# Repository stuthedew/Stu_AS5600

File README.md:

# Stu_AS5600
Arduino Library AS5600 12-bit Programmable Contactless Potentiometer

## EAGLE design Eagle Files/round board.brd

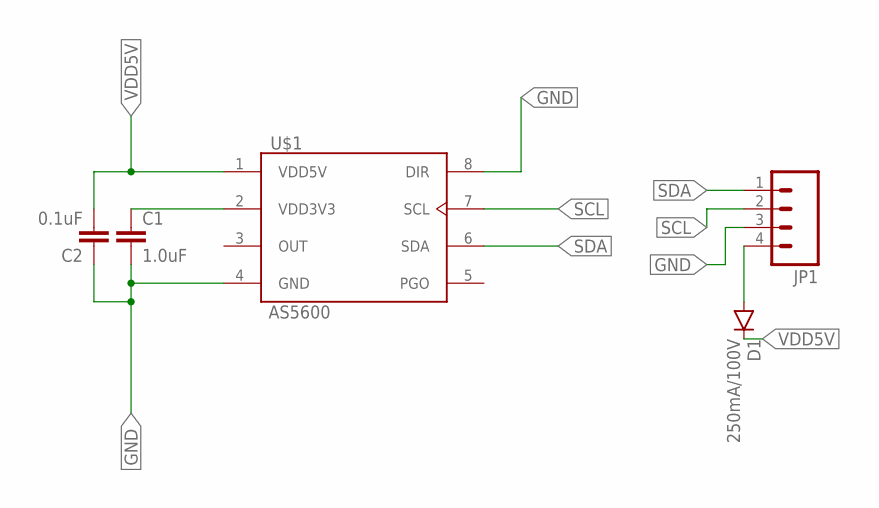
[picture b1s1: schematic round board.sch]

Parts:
C1: 1.0uF; 0603-CAP
C2: 0.1uF; 0603-CAP
D1: 250mA/100V; SOD-323
JP1: M04LOCK; 1X04_LOCK
U$1: AS5600; SOIC8

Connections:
GND: C1.2, C2.1, JP1.3, U$1.4 (GND), U$1.8 (DIR)
unnamed: C1.1, U$1.2 (VDD3V3)
unnamed: D1.A, JP1.4
SCL: JP1.2, U$1.7 (SCL)
SDA: JP1.1, U$1.6 (SDA)
VDD5V: C2.2, D1.C, U$1.1 (VDD5V)

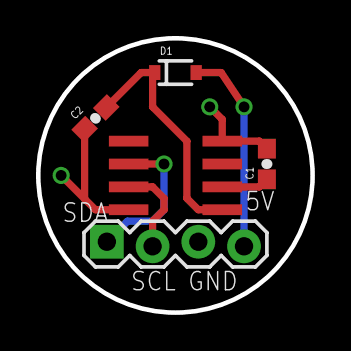
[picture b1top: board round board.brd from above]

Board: 2 copper layers, 15.2 x 15.2 mm, 5 parts (0 on the bottom side), 6 nets.

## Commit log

2015-02-09 Added Datasheet
2015-02-15 Changed dev branch name for test .ino file
    Fixed conflict with .cpp file and .ino file having the same name.
2015-02-15 Added more definitions
2015-02-15 Testing sketch
2015-02-16 Working
2015-02-16 created eagle board
2015-02-16 Adjusted silk screen
2015-02-16 Moved AS5600 footprint to center of board (v1.1)
    Removed pull-up resistors

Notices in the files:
parts and their libraries:
SparkFun-Connectors: Licensing: Creative Commons ShareAlike 4.0 International - https://creativecommons.org/licenses/by-sa/4.0
